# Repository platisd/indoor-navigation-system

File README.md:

# Indoor Navigation System  

[WIP] An indoor navigation system that guides you to the desk of your colleagues.

## What?
INS is a navigation system that utilizes a fleet of portable embedded devices, which can be located, to guide its user towards the desk of an employee or a colleague. The main scenario begins by searching for an employee on a mobile client. Then the system provides information regarding the whereabouts of the said employee's desk as well as navigational instructions on how to reach it.

The system does not intend to monitor individuals, but merely broadcast their currently designated workspace. The tracking nodes are not meant to be constantly carried along, but placed on the desk where someone is working on and forgotten until their owner changes desk.

## Why?
Medium and large organizations involve office settings where employees are spread out throughout different floors. It is typically difficult to locate personnel with whom there is infrequent physical collaboration. The challenge becomes even greater when employees either do not possess a dedicated work-area or tend to move between locations. The main advantage of INS is that it provides dynamic updates in case the position of an employee's workspace changes, voiding the need for any manual action from  the employee's side.

What is possibly more important is the technology developed within this context, can be easily reused in different occasions, such as in IoT and indoor positioning applications.

## How?
A fleet of portable devices, transmit the signal strength (RSSI) of their surrounding WiFi access points (AP) to a central server. Since the exact location of the various APs is known, we can utilize the provided data to pinpoint the nodes within the building. Finally, a user can fetch the calculated location from the server using a mobile client.

INS is a distributed system composed of the following layers that communicate via HTTP requests:
* [Node](/ins-node)
  * A portable device that transmits the signal strengths it detects. It is comprised of a WiFi Module that handles the connectivity and a Power Module that determines when the node should go to sleep to minimize its power consumption.
* [Server](/server)
  * A REST server that receives the RSSI signals, calculates the location of each node and supplies the information to the interested parties.
* [Client](/ins-app)
  * A mobile client that visualizes the location of the inquired employee and guides its user towards that location.

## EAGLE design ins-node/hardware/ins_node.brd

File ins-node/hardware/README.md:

# INS-node hardware
INS-node board schematics and layout designed with Eagle CAD.

## Features
* UART connection between power controller MCU and WiFi module
* N-channel MOSFETs to control the power
* 1 LED for power controller MCU
* 1 LED for WiFi module
* Decoupling capacitors
* Reset button for power controller MCU
* Drawing area for node id
* Mounting holes for M3 screws

## 2D board renders
* Top view

* Bottom view

## List of materials
* Wemos D1 Mini
* ATtiny85
* 3 x AAA battery holders
* 2 x 2N7000 N-channel MOSFET
* 2 x 220 Ohm resistors
* 2 x 4.7 KOhm resistors
* 0.1 uF capacitor
* 2 x 5mm LED
* SPST tactile switch

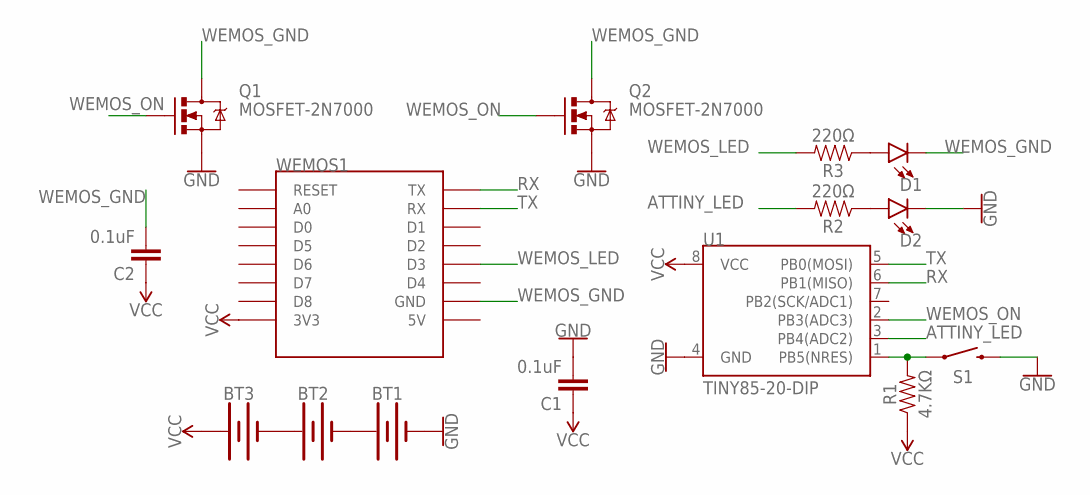
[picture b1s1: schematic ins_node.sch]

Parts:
BT1, BT2, BT3: BATTERY-AAA
C1, C2: 0.1uF; CAP-PTH-SMALL-KIT
D1, D2: LED5MM-KIT; LED_5MM-KIT
Q1, Q2: MOSFET-2N7000; TO-92
R1: 4.7KΩ; AXIAL-0.3
R2, R3: 220Ω; AXIAL-0.3
S1: MOMENTARY-SWITCH-SPST-PTH-6.0MM; TACTILE_SWITCH_PTH_6.0MM
U1: TINY85-20-DIP; DIP08_MCU
WEMOS1: WEMOS-D1-MINI

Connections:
ATTINY_LED: R2.P$2 (2), U1.3 (PB4(ADC2))
GND: BT1.GND@1 (-), C1.2, D2.K (C), Q1.1 (S), Q2.1 (S), S1.3 (2), U1.4 (GND); also elsewhere on the board
unnamed: BT1.PWR@1 (+), BT2.GND@1 (-)
unnamed: R1.P$2 (2), S1.1, U1.1 (PB5(NRES))
unnamed: D1.A, R3.P$1 (1)
unnamed: D2.A, R2.P$1 (1)
unnamed: BT2.PWR@1 (+), BT3.GND@1 (-)
RX: U1.6 (PB1(MISO)), WEMOS1.TX
TX: U1.5 (PB0(MOSI)), WEMOS1.RX
VCC: BT3.PWR@1 (+), C1.1, C2.1, R1.P$1 (1), U1.8 (VCC), WEMOS1.3V3
WEMOS_GND: C2.2, D1.K (C), Q1.3 (D), Q2.3 (D), WEMOS1.GND
WEMOS_LED: R3.P$2 (2), WEMOS1.D3
WEMOS_ON: Q1.2 (G), Q2.2 (G), U1.2 (PB3(ADC3)); also elsewhere on the board

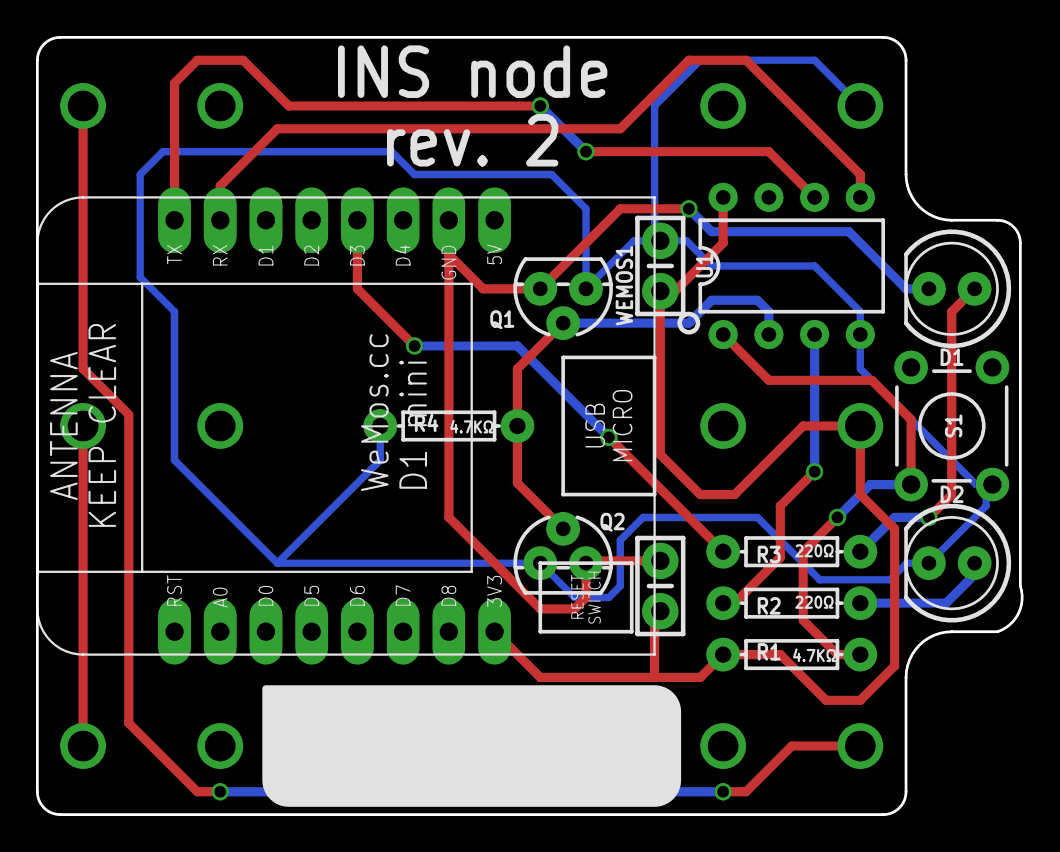
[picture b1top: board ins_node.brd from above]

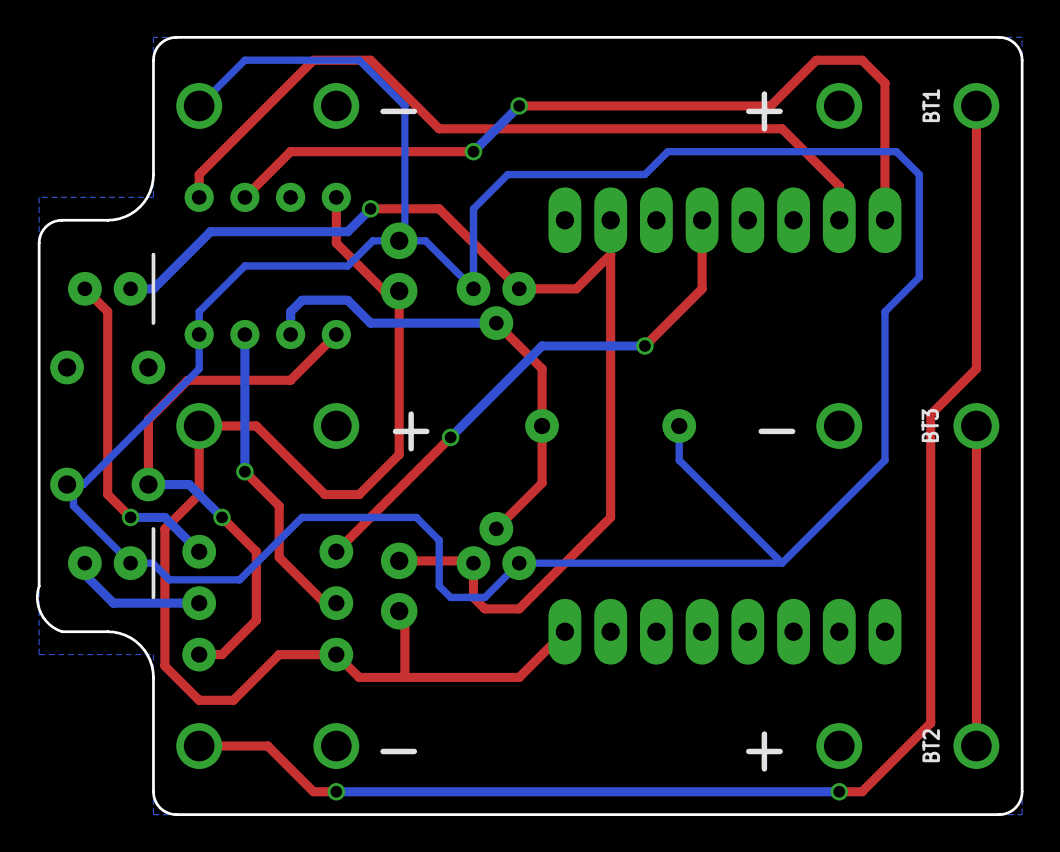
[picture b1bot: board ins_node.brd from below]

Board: 2 copper layers, 54.7 x 43.2 mm, 16 parts (3 on the bottom side), 13 nets.

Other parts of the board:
R4: 4.7KΩ; AXIAL-0.3

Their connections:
GND: R4.P$1; also elsewhere on the board
WEMOS_ON: R4.P$2; also elsewhere on the board

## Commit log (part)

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2016-12-21 Fixes to make it build
    Changed fetching source from the 0.0.1 release to the latest master
    Find the Package Threads, otherwise lpthreads does not seem to link
2016-12-23 Updated README.md
    Author: platisd <kurukii88@gmail.com>
2016-12-23 Small refactoring and placeholder for the mock class
2017-01-04 Some refactoring
2017-01-05 updated gitignore
2017-01-05 small correction
2017-01-07 Manual control test
2017-01-07 cmake iterates through the unit tests folder succesfully
2017-01-08 some first changes
2017-01-08 Adding more mocks and other small updates
2017-01-08 Adding motor mocks
2017-01-09 Revert "Adding motor mocks"
    This reverts commit 1f26d2d16a45347ecf6d00e51b20c8ad1b6347de.
2017-01-09 Revert "Revert "Adding motor mocks""
    This reverts commit d5361462667fffe49264741f93b5995256942272.
2017-01-09 adding more stuff
2017-01-09 More example tests and checks if sensors have been attached
2017-01-10 Restructured examples
2017-01-10 Adding readme files
2017-01-10 Moved build script to root folder
2017-01-18 First try for Windows batch script
    Using g++ and make through mingw
2017-01-19 Pulling Arduino-Mock from forked repo that includes additional Serials
    This until the pull request is accepted
2017-01-25 Various corrections
    * Odometer attach now does not set the odometer as attached if an invalid interrupt pin is used
    * Additional attach function according to Smartcar library v. 4.1.0
    * Returns added where it was forgotten
2017-01-28 Removing smartcar_mock so to add it as a submodule
    For easier updates
2017-01-28 Update to latest smartcar mock
    You can also do this by running:
    git submodule foreach git pull origin master
2017-01-28 Including a fix for a probable git error
2017-01-29 typo fix
2017-08-17 Add example for multiple sensors
2017-10-18 Update REAME.md with dep. & build information
2017-10-19 Move server related files into separate directory.
    Issue #2
2017-10-19 Set CMake version to 3.2
    To make it easier to build in Travis CI
2017-10-19 Update README
    * Aesthetic changes mostly
    * Added build status icon
2017-10-23 Remove dependency to Spdlog
    * Fixes 11
    * Minor code restructure
2017-10-23 Modify get_dependencies.sh script
2017-10-25 Fix returned undefined position
    * Fixes #13
    * Return error msg to client when query result is empty.
2017-10-26 Initial ins-node directory
    Related to #16
2017-10-26 Move testing structure into ins-node
    Related to #16
2017-10-26 Remove unrelated examples
    Related to #16
2017-10-26 Add initial ins-node sketch and test
    * Minor changes to cmakelists to compile
    * Added test_utils.h to include small stubs etc
    for Arduino compatibility.
    Related to #16
2017-10-26 Adjust scripts for CI build
    Related to #16
2017-10-27 Move thirdparty library into include/external dir
    Preparing delivery for #15
2017-10-27 Add gtest-gmock test framework
    Related to #15
2017-10-27 Refactoring ...
    * Update header guards
    * Change code format based on new .clang-format
    * Use one logger instance instead of one per class
    * Declare UT classes as friend class
    * Related to #15
2017-10-27 Add build_and_run_ut.sh
    * Fixes #15
2017-10-27 Update .travis.yml
    Use server/build_and_run_ut.sh script
2017-10-27 Change to c++11
    * Related to #15
2017-10-28 Modern c++ settings for Travis
2017-10-28 back to c++14
2017-10-28 Revert "Remove build.sh"
    This reverts commit 9e6858cb3e9401bb18f157b658fe8f06bdcd41ab.
2017-10-29 Add INS-node board prototype
    Fixes #19
2017-10-29 Add decoupling capacitor
2017-10-31 Separate source folders for ins-node
    * Power controller MCU and Wifi module sketches placed
    in separate folders
    * Updates tests
    * Renamed test_utils.h
    This new structure is additionally more on par with how
    Arduino IDE handles sketches (i.e. sketch_name/sketch_name.ino)
2017-11-02 Fix wrong use of ssid.
2017-11-07 Add new REST action, Modify database schema
    * Adds a new REST url to trigger resolution of device's position
    * Simplify database table schema for device
    * Update REST API
    * Other minor changes
    * Fixes issue #27
    * Fixes issue #28
2017-11-07 Minor update & fixes.
2017-11-10 Fix wifi module powering issues
    HW rev.1 includes:
    * 2 MOSFETs for driving the wifi module
    * 3 AAA batteries
    * Additional decoupling capacitor
    * Board restructuring as a result of new components
    Fixes #29
2017-11-11 Update battery position and orientation for consistency
2017-11-14 Add interrupts header for completeness
2017-11-14 Get almost everything to compile without tests
2017-11-14 Add interrupts stub
2017-11-14 Add header stubs
2017-11-14 Add initial power manager firmware
    * TO-DO: Update wifi off and on times
    * TO-DO: Implement shutdown prevention strategy
    Fixes #23
2017-11-15 Add tests
2017-11-15 Fix test case names for consistency
2017-11-16 Add function to read distinct mac addr from db.
2017-11-16 UT for DataStore class
    * Minor fixes
    * Partly fixes #39
2017-11-16 Add DataStore mock class
    * Related to #39
2017-11-16 Update number of batteries used
2017-11-19 Add lcov initial structure
    * Currently reports for ins-node
    * Missing uploading to codecov.io
    * Missing reports for server
2017-11-19 Ignore pistache if downloaded locally
2017-11-19 Make script executable
2017-11-19 Upload coverage reports to codecov
2017-11-19 Add code coverage badge
2017-11-20 Define path to coverage report
    Force codecov to read the specific code coverage report
    which we have already generated so to enforce the ignored
    filepaths list. Alternatively, which is actually the suggested
    way of doing this, one should create a `.codecov.yml` file as
    described [here](https://docs.codecov.io/v4.3.6/docs/ignoring-paths).
    However, since we probably don't want to completely rely on
2017-11-20 Add code of conduct document
    Fixes #45
2017-11-21 Wifi_node - prototype
2017-11-21 Add issue template
    Fixes #51
2017-11-21 Delete PULL_REQUEST_TEMPLATE.md
    sorry, merged this directly to the `dev` branch, deleting it to create a pull request instead.
2017-11-21 Add pull request template
    Developers will now see this template when opening a new pull request which will help us promote consistency on how we merge code in INS.
    Fixes #50
2017-11-21 Add Localization mock class
    * Relates to #39
2017-11-21 Add wrapper class for better testing
    * Makes specific calls to Pistache library testable
2017-11-21 Fix DataStore mock class
2017-11-21 Add UT for DataStore & InsService
    * Relates to #39
2017-11-21 Update CMake files and Refactor InsService
    * Relates to #39
2017-11-21 Remove redundant header files
2017-11-22 Fix dependency to spdlog
    For our builds we were not using the spdlog library that is
    found inside server/include/external. Because of this, build
    would not work unless spdlog was already installed in the
    system. Now Travis is set to build the server so to avoid
    such problems in the future.
    Fixes #57
2017-11-23 Corrections based on comments in #55
2017-11-24 Change RSSI datatype to int32_t
    * Solves #62
2017-11-25 Create AccessPoint table
2017-11-25 Add AccessPoint class type
2017-11-26 Refac: Add AccessPoint datatype
2017-11-28 Fix failing unit test
2017-12-03 Change wifi module header file name
    This is done in order to make it more obvious
    as to its use.
2017-12-03 Add main Wifi module logic
    #44
2017-12-03 Remove wifi credentials from version control
    We don't want people to accidentally push their
    private data (e.g. wifi SSID or passwords)
2017-12-03 Add tests
    Tested the following methods:
    * setup
    * getNetworkContext
    * getDatapoints
2017-12-03 Add test for transmitData()
2017-12-03 Remove unnecessary constructor and destructor
2017-12-03 Add initial mock
2017-12-03 Clang format the tests
2017-12-03 Remove unused function
2017-12-03 Make SERVER_IP local variable
2017-12-03 Fix TCP request URI contents
2017-12-03 Build tests with C++14
2017-12-03 Add tests for loop()
2017-12-03 available() to return int
    Change to increase consistency to the original API
2017-12-03 Fix retries and post request syntax
2017-12-03 Small identation fix
    Just to make everything look perfect...
2017-12-05 Fix WiFi Module power pin according to schematics
    Fixes #66
2017-12-05 Fix negative voltage when Wifi module is off
    When the WiFi module was turned off, the power controller did not have
    a common ground with the wifi module, which would cause the relative
    voltage (from the wifi module's perspective) to be negative. This would
    strangely result in a constant low voltage of around 1-1.5 volts being
    present at the VCC and GND pins of the WiFi module. This resulted in
    weird behavior and overall needlessly higher power consumption.
2017-12-05 Add pulldown resistor for MOSFETs base
    Add a pulldown resistor for the MOSFET trigger pins so to make sure
    that we have a clean signal that only activates the Wifi module
    when we want.
    This change constitutes HW Rev. 2
    Fixes #71
2017-12-22 Execute GET requests for specified node on press
    On button press a GET request is sent to the local Python + Flask
    server (i.e. not the INS one) for testing and verification purposes.
    Should be later changed to the correct URI.
2017-12-22 Update to JAVA 8
2017-12-22 Ignore .idea folder
    This folder often includes developer-specific attributes and therefore
    I cannot find any good reason as to why it should be version controlled.
2017-12-24 Add coverage reports for ins-app
    Introduces coverage report for the Android application and makes
    sure that codecov only parses the generated reports and not the
    whole project (this is done so to force coverage only on specific
    filepaths and not uninteresting files such as external libraries).
2017-12-29 Use android target version as a variable
2017-12-29 Run tests with info flag
2017-12-29 Add coverage reports for unit tests
2017-12-30 Respond with a well-formed JSON on position requests
    This is done so to make parsing easier on the client side.
2017-12-30 Parse the server response as JSON
2017-12-30 Split request url to separate variables
    Since the server IP and port will eventually change, let's have them
    as separate variables to increase modifiability.
2017-12-31 Update installations instructions
    Use the ATtinyCore board support package instead
2018-01-08 Add project description
    Fixes #76
2018-01-09 Fix wording
    Let's not confuse the reader with technical details at this point.
2018-01-13 Add initial pistache mock
    Since we need to have a folder called pistache we cannot gitignore it.
    From now on, the pistache repository will be clones into a folder called
    and the folder will contain the mocks.
2018-01-15 Add initial stubs to be mocked
    * Missing the bind stub (probably most important)
    * Some of the signatures will need to be changed
    * Some functions might need to provide sample implementation
    * Have not tested yet for syntax errors
2018-01-17 Use std::signal and csignal header
    * Fixes #85
2018-01-18 Integrate Travis notifications to Slack
    Fixes #88
2018-01-20 Add more stubs and fakes
2018-01-22 Upgrade to clang4-0 and explicitly add cmake tool
    Affects Issue #90
    * Setup CI environment for upcoming changes in #90
2018-01-22 Updating travis.yml
2018-01-22 Extend get_dependency script to install cmake 3.10
2018-01-22 Add cpp static analysis check to ins server
    Affects #90
    * Clang-tidy will be used to statically analyze all cpp translation units
    under repo/server/src
    * This is done for every run on server/build.sh script
    * Using all clang-tidy bundled checkers
    * No verdict for builds with warnings.
2018-01-22 Fix server/build.sh to propagate exit status to bash
    * Without this fix, Travis reports success even when
    server/build.sh fails
2018-01-22 Fix syntax issue raised by clang-tidy
    * Affects #90
    * Commit should take care of clang-tidy warning except
    warning related to cppcoreguidelines-pro-bounds-pointer-arithmetic
2018-04-20 [INS] Cosmetic changes
2018-04-20 [INS] fixed wifi no. sample data derefencing bug.
2018-04-21 [INS] cosmetic changes and fixed rssi data buffer bug.
2018-04-22 [INS] Included Dimitrios' Requested Changes.
2018-04-22 [INS] Added libxml header files for failing tests [ ${LIBXML2_INCLUDE_DIR} var works for main sw build but not test build :( ].
2018-04-22 [INS] reverted previous changes. i.e Added libxml header files for failing tests [ ${LIBXML2_INCLUDE_DIR}. investigate if findpackage must come earlier.
2018-04-23 [INS] Further WifiNode cleanup.
2018-07-18 Added more comments in wifinode API and other cosmetic changes per Dimitrios' suggestions.

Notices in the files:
parts and their libraries:
SparkFun-Retired: Licensing: Creative Commons ShareAlike 4.0 International - https://creativecommons.org/licenses/by-sa/4.0
